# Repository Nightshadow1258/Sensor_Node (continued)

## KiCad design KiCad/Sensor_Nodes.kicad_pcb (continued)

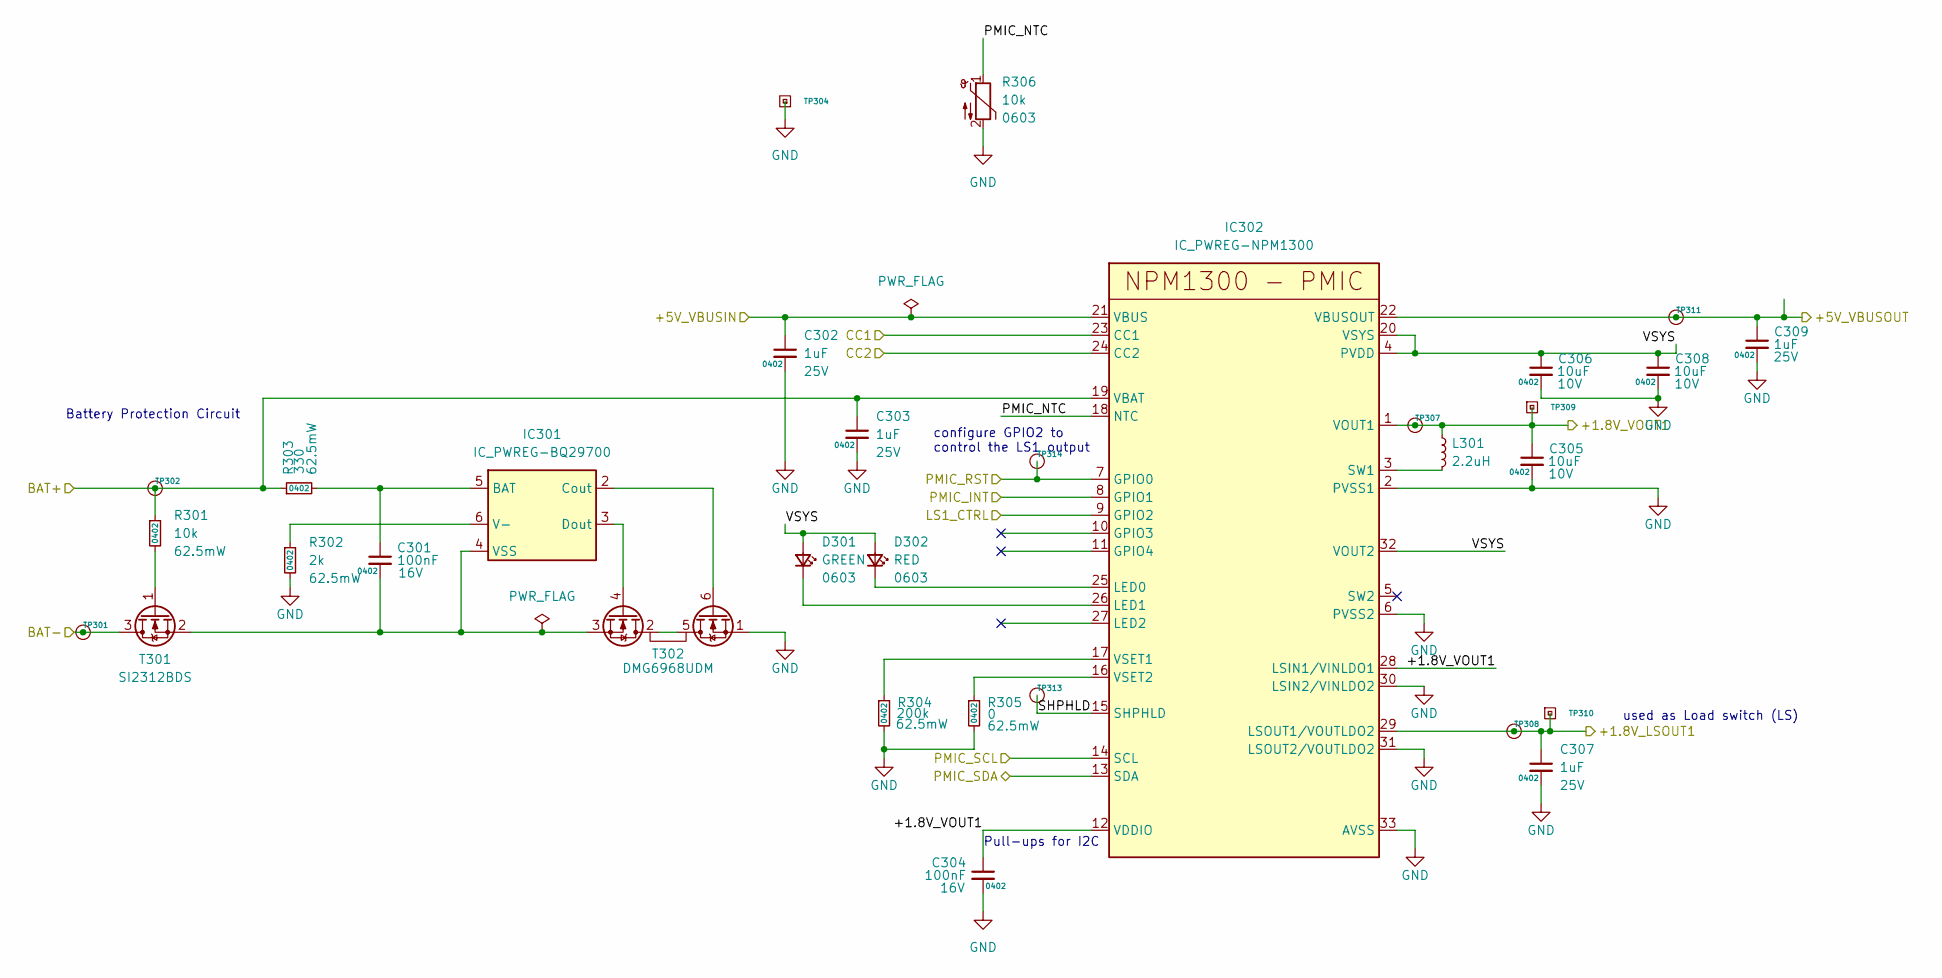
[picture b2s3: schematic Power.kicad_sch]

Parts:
C301, C304: 100nF; C_0402_1005Metric; Voltage 16V; LCSC Part # C1525
C302, C303, C307, C309: 1uF; C_0402_1005Metric; Voltage 25V; LCSC Part # C52923
C305, C306, C308: 10uF; C_0603_1608Metric; Voltage 10V; LCSC Part # C96446
D301: GREEN; D_0603_1608Metric; LCSC Part # C72043
D302: RED; D_0603_1608Metric; LCSC Part # C2286
IC301: IC_PWREG-BQ29700; WSON-6_1.5x1.5mm_P0.5mm; LCSC Part # C183096
IC302: IC_PWREG-NPM1300; QFN-32-1EP_5x5mm_P0.5mm_EP3.6x3.6mm_ThermalVias
L301: 2.2uH; L_0806; LCSC Part # C2838367
R301: 10k; R_0402_1005Metric; Power Rating 62.5mW; LCSC Part # C25744
R302: 2k; R_0402_1005Metric; Power Rating 62.5mW; LCSC Part # C4109
R303: 330; R_0402_1005Metric; Power Rating 62.5mW; LCSC Part # C25104
R304: 200k; C_0402_1005Metric; Power Rating 62.5mW; LCSC Part # C25764
R305: 0; R_0402_1005Metric; Power Rating 62.5mW; LCSC Part # C17168
R306: 10k; R_0603_1608Metric; LCSC Part # C142556
T301: SI2312BDS; SOT-23; LCSC Part # C351405
T302: DMG6968UDM; SOT-23-6; LCSC Part # C2762931
TP301, TP302, TP307, TP308, TP311, TP313, TP314: TP; TP_Pad_D0.9mm
TP304, TP309, TP310: Testpoint-BASE; TP_THT_D0.8mm

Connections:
/MCU/+1.8V_LS1: C307.1, IC302.29 (LSOUT1/VOUTLDO2), TP308.1, TP310.1; also elsewhere on the board
/MCU/+1.8V_VDD_nRF: C304.1, C305.1, IC302.1 (VOUT1), IC302.12 (VDDIO), IC302.28 (LSIN1/VINLDO1), L301.1, TP307.1, TP309.1; also elsewhere on the board
/MCU/+3.7V_BAT: C303.1, IC302.19 (VBAT), R301.1, R303.1, TP302.1; also elsewhere on the board
/MCU/+5V_VBUS: C309.1, IC302.22 (VBUSOUT), TP311.1; also elsewhere on the board
/MCU/LS1_CTRL: IC302.9 (GPIO2); also elsewhere on the board
/MCU/NRF_PMIC_RST: IC302.7 (GPIO0), TP314.1; also elsewhere on the board
/MCU/NRF_PMIC_SCL: IC302.14 (SCL); also elsewhere on the board
/MCU/NRF_PMIC_SDA: IC302.13 (SDA); also elsewhere on the board
/MCU/NRF_PRMIC_INT: IC302.8 (GPIO1); also elsewhere on the board
/POWER/+5V_VBUSIN: C302.1, IC302.21 (VBUS); also elsewhere on the board
/POWER/BAT-: T301.3 (D), TP301.1; also elsewhere on the board
/POWER/CC1: IC302.23 (CC1); also elsewhere on the board
/POWER/CC2: IC302.24 (CC2); also elsewhere on the board
/POWER/PMIC_NTC: IC302.18 (NTC), R306.1
/POWER/SHPHLD: IC302.15 (SHPHLD), TP313.1
/POWER/VSYS: C306.1, C308.1, D301.2 (A), D302.2 (A), IC302.4 (PVDD), IC302.20 (VSYS), IC302.32 (VOUT2)
GND: C302.2, C303.2, C304.2, C305.2, C306.2, C307.2, C308.2, C309.2, IC302.2 (PVSS1), IC302.6 (PVSS2), IC302.30 (LSIN2/VINLDO2), IC302.31 (LSOUT2/VOUTLDO2), IC302.33 (AVSS), R302.2, R304.2, R305.2, R306.2, T302.1 (S1), TP304.1; also elsewhere on the board
unnamed: D301.1 (K), IC302.26 (LED1)
unnamed: D302.1 (K), IC302.25 (LED0)
unnamed: C301.1, IC301.5 (BAT), R303.2
unnamed: IC301.2 (Cout), T302.6 (G1)
unnamed: IC301.3 (Dout), T302.4 (G2)
unnamed: IC301.6 (V-), R302.1
unnamed: C301.2, IC301.4 (VSS), T301.2 (S), T302.3 (S2)
unnamed: IC302.3 (SW1), L301.2
unnamed: IC302.17 (VSET1), R304.1
unnamed: IC302.16 (VSET2), R305.1
unnamed: R301.2, T301.1 (G)
unnamed: T302.2 (D1/D2), T302.5 (D1/D2)

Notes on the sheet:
Pull-ups for I2C
Battery Protection Circuit
configure GPIO2 to control the LS1 output
used as Load switch (LS)

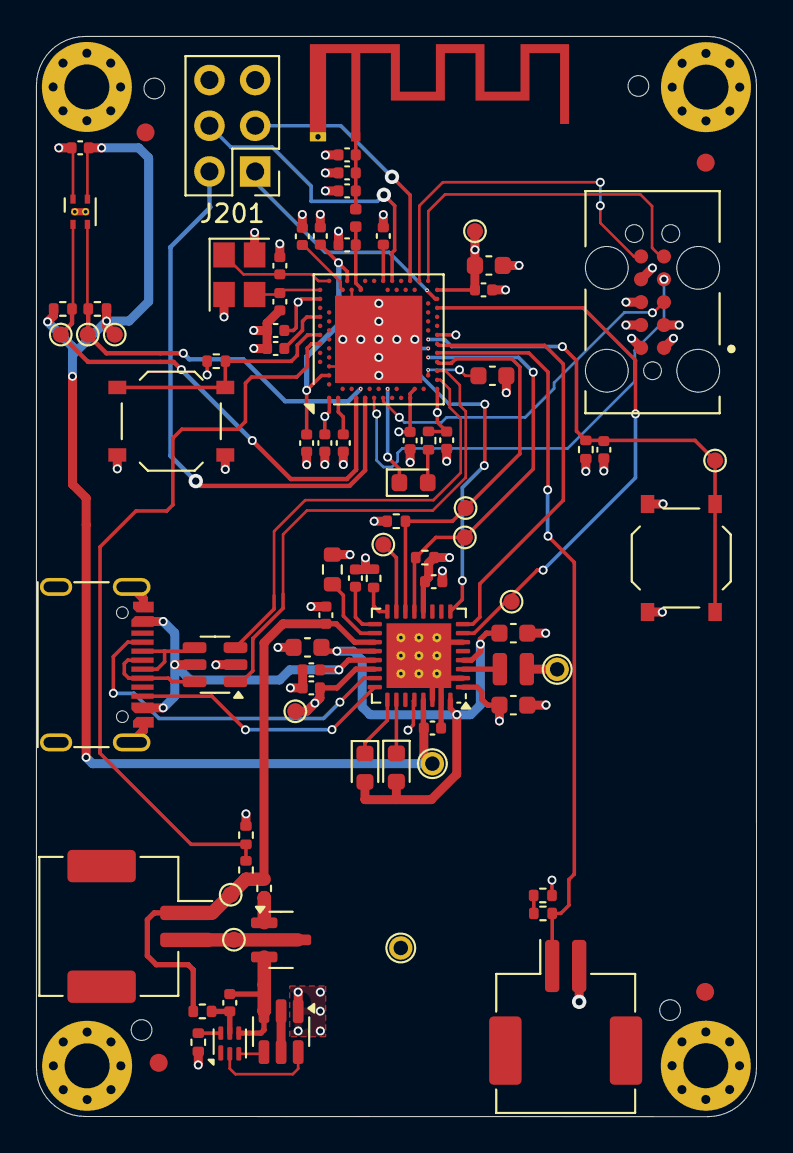
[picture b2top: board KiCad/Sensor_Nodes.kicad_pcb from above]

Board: 4 copper layers, 40.0 x 60.0 mm, 95 parts (0 on the bottom side), 60 nets.

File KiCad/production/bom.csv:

Designator,Footprint,Quantity,Value,LCSC Part #
AE201,Texas_SWRA117D_2.4GHz_Right,1,Antenna_Shield,
"C201, C205",0402,2,12pF,C1547
C202,0402,1,10nF,C15195
"C203, C215",0402,2,1uF,C15525
"C204, C219, C305, C306, C308",0603,5,10uF,C96446
"C206, C207, C208, C212, C214, C217, C218, C220, C221, C301, C304",0402,11,100nF,C1525
C209,0402,1,0.8pF, C327032
"C210, C211",0402,2,0.5pF,C285052
C213,0402,1,1.2pF,
C216,0402,1,100pF,C1546
"C302, C303, C307, C309",0402,4,1uF,C52923
CON101,CON-GEN-USB_C-16P,1,G Switch GT USB 7010ASV,C2988369
"CON102, CON103",CON-SM02B-ZESS_TB,2,SM02B-ZESS-TB,
CON201,CON-TAG-CONNECT_TC2050-IDC,1,TC2050-FP,
D101,SOT-23-6,1,USBLC6-2,C7519
D201,0603,1,BLUE,C72041
D301,0603,1,GREEN,C72043
D302,0603,1,RED,C2286
"FID101, FID102, FID103, FID104",Fiducal-JLCPCB,4,Fiducal-JLCPPCB,
IC201,Nordic_AQFN-73-1EP_7x7mm_P0.5mm,1,NRF52840,C190794
IC202,DNF-1.5x1.5_H0.54-SHT40-AD1B_THPAD,1,IC_SENS-SHT40-AD1B_THP,
IC301,WSON-6_1.5x1.5mm_P0.5mm,1,IC_PWREG-BQ29700,C183096
IC302,QFN-32-1EP_5x5mm_P0.5mm_EP3.6x3.6mm_ThermalVias,1,IC_PWREG-NPM1300,
J201,PinHeader_2x03_P2.54mm_Vertical,1,Conn_02x03_Odd_Even,
L201,0402,1,4.7nH,C370227
L301,L_0806,1,2.2uH,    C2838367
"MH101, MH102, MH103, MH104",MountingHole_2.5mm_Pad_Via,4,~,
"PCB101, PCB102, PCB103, PCB104",PCB-NPTH-JLCPCB,4,Tooling Hole JLCPCB,
R201,0402,1,1k,C11702
"R202, R209, R301",0402,3,10k,C25744
"R203, R205, R210",0402,3,1M,C138033
"R204, R206, R207, R208",0402,4,4k7, C25900
R211,0402,1,750k,C137937
R302,0402,1,2k,C4109
R303,0402,1,330,C25104
R304,0402,1,200k,C25764
R305,0402,1,0,C17168
R306,0603,1,10k,C142556
"SW201, SW202",SW-PUSH-DPST-XKS-TS-1187A,2,SW-GEN-TS-1187A,C318884
T301,SOT-23,1,SI2312BDS, C351405 
T302,SOT-23-6,1,DMG6968UDM, C2762931
"TP201, TP202, TP203, TP204, TP205, TP301, TP302, TP307, TP308, TP311, TP313, TP314",TP_Pad_D0.9mm,12,TP,
"TP304, TP309, TP310",TP_THT_D0.8mm,3,Testpoint-BASE,
X201,Crystal_SMD_3225-4Pin_3.2x2.5mm,1,32MHz,C2901708

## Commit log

2025-07-28 Commit of Version 1.00 data.
2025-07-30 Add Version 1
2025-07-30 clean up of hidden files
2025-07-30 Initial commit for V2.00
2025-07-30 Inital commit for V3.00
2025-07-30 Initial commit for V3.00
2025-08-13 Added pdf export to Documents folder.
2025-08-13 Add nicer photos.
2025-08-13 Added nice photo.
2025-08-13 Add nice photo.
